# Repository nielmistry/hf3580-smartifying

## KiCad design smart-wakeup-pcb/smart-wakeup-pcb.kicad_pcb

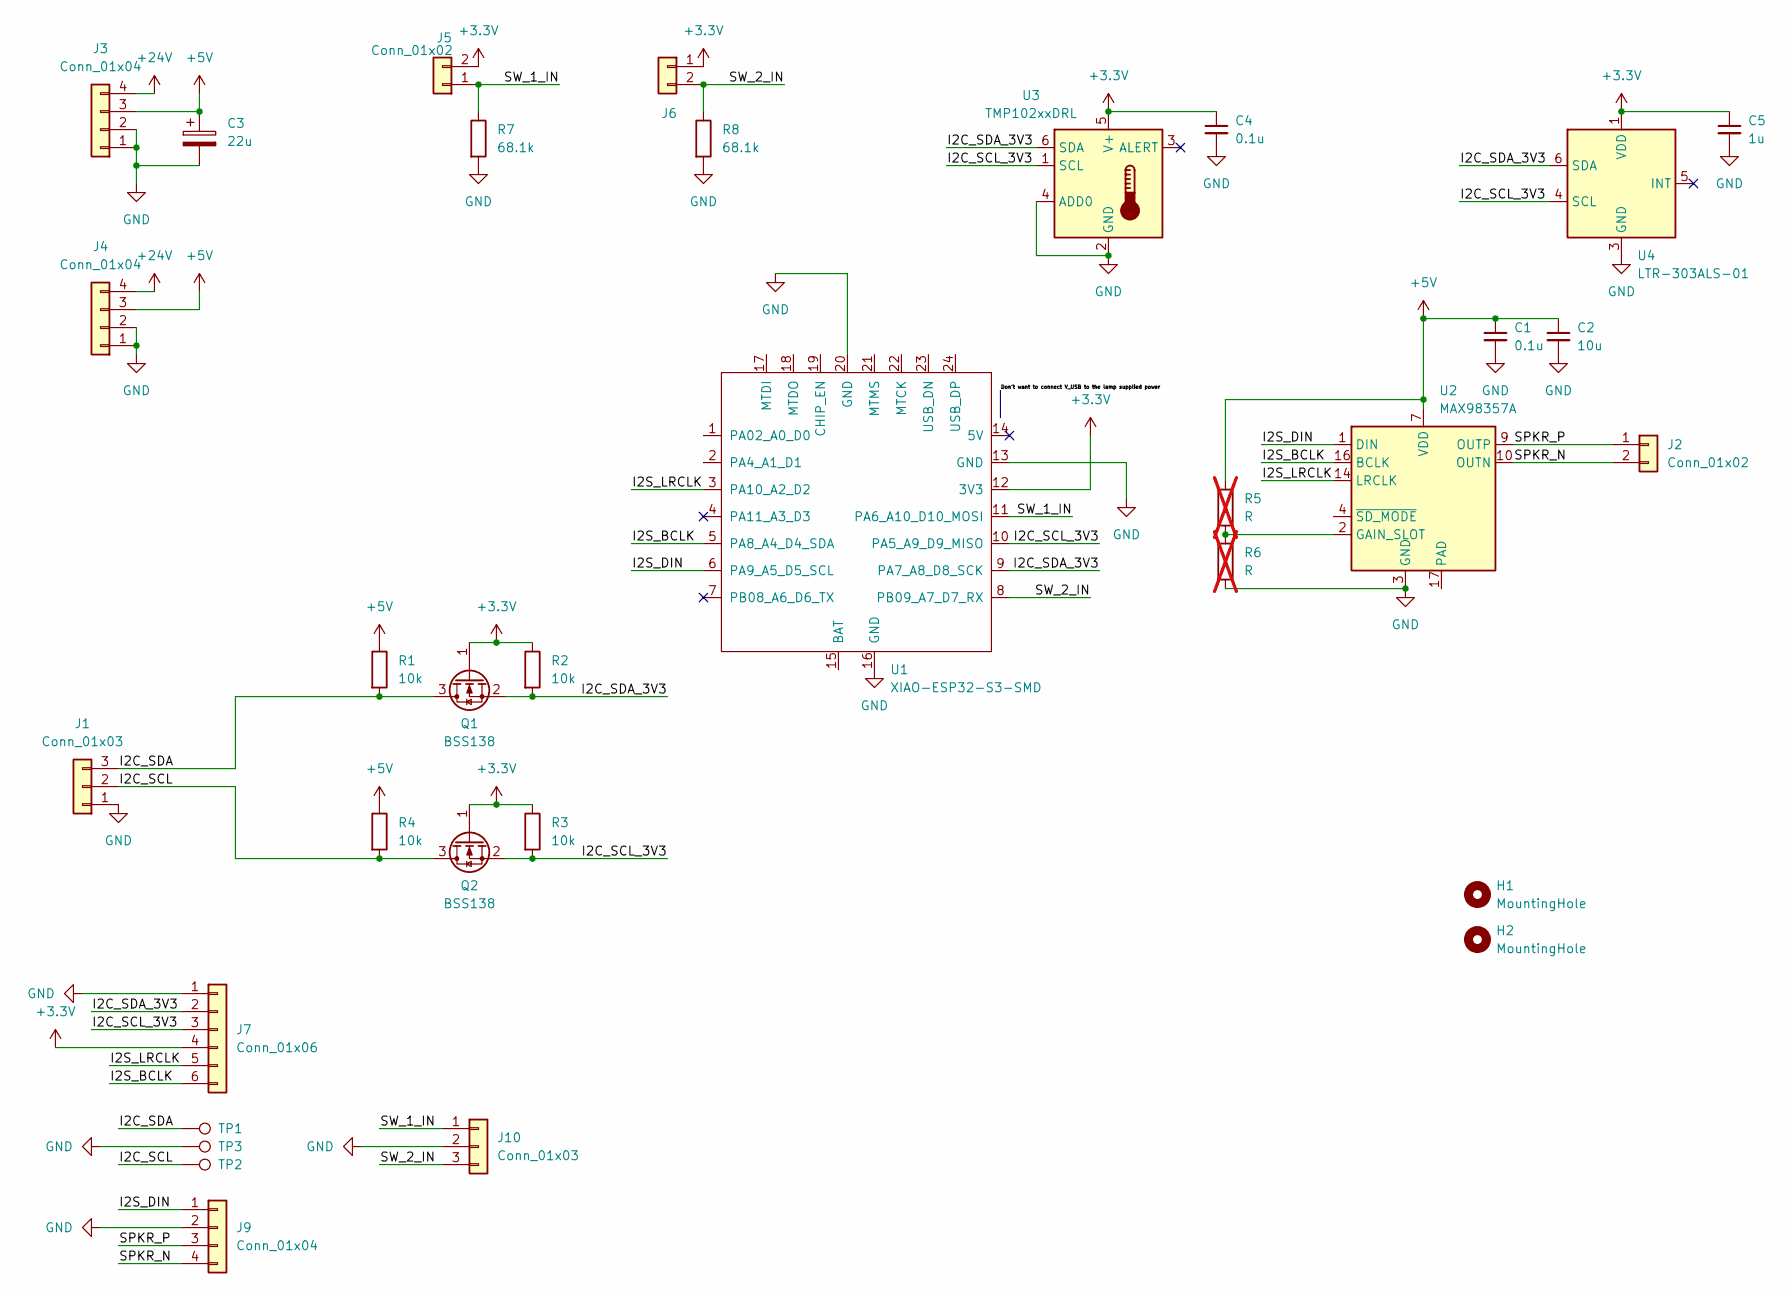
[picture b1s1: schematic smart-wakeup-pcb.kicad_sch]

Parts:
C1, C4: 0.1u; C_0603_1608Metric
C2: 10u; C_0603_1608Metric
C3: 22u; CP_Radial_D5.0mm_P2.00mm
C5: 1u; C_0603_1608Metric
H1, H2: MountingHole; MountingHole_2.2mm_M2
J1: Conn_01x03; JST_PH_S3B-PH-K_1x03_P2.00mm_Horizontal
J2: Conn_01x02; JST_PH_S2B-PH-K_1x02_P2.00mm_Horizontal
J3, J4: Conn_01x04; JST_PH_S4B-PH-K_1x04_P2.00mm_Horizontal
J5, J6: Conn_01x02; JST_PH_B2B-PH-K_1x02_P2.00mm_Vertical
J7: Conn_01x06; PinHeader_1x06_P1.00mm_Vertical
J9: Conn_01x04; PinHeader_1x04_P1.00mm_Vertical
J10: Conn_01x03; PinHeader_1x03_P1.00mm_Vertical
Q1, Q2: BSS138; SOT-23
R1, R2, R3, R4: 10k; R_0603_1608Metric
R5, R6: R; R_0603_1608Metric; not fitted
R7, R8: 68.1k; R_0603_1608Metric
TP1, TP2, TP3: TestPoint; TestPoint_Pad_D1.5mm
U1: XIAO-ESP32-S3-SMD
U2: MAX98357A; TQFN-16-1EP_3x3mm_P0.5mm_EP1.23x1.23mm
U3: TMP102xxDRL; SOT-563
U4: LTR-303ALS-01; Lite-On_LTR-303ALS-01

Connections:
+3.3V: C4.1, C5.1, J5.2, J6.1, J7.4, Q1.1 (G), Q2.1 (G), R2.1, R3.1, U1.12 (3V3), U3.5 (V+), U4.1 (VDD)
+5V: C1.1, C2.1, C3.1, J3.3, J4.3, R1.1, R4.1, R5.1, U2.7 (VDD), U2.8 (VDD)
+24V: J3.4, J4.4
/I2C_SCL: J1.2, Q2.3 (D), R4.2, TP2.1
/I2C_SCL_3V3: J7.3, Q2.2 (S), R3.2, U1.10 (PA5_A9_D9_MISO), U3.1 (SCL), U4.4 (SCL)
/I2C_SDA: J1.3, Q1.3 (D), R1.2, TP1.1
/I2C_SDA_3V3: J7.2, Q1.2 (S), R2.2, U1.9 (PA7_A8_D8_SCK), U3.6 (SDA), U4.6 (SDA)
/I2S_BCLK: J7.6, U1.5 (PA8_A4_D4_SDA), U2.16 (BCLK)
/I2S_DIN: J9.1, U1.6 (PA9_A5_D5_SCL), U2.1 (DIN)
/I2S_LRCLK: J7.5, U1.3 (PA10_A2_D2), U2.14 (LRCLK)
/SPKR_N: J2.2, J9.4, U2.10 (OUTN)
/SPKR_P: J2.1, J9.3, U2.9 (OUTP)
/SW_1_IN: J5.1, J10.1, R7.1, U1.11 (PA6_A10_D10_MOSI)
/SW_2_IN: J6.2, J10.3, R8.1, U1.8 (PB09_A7_D7_RX)
GND: C1.2, C2.2, C3.2, C4.2, C5.2, J1.1, J3.1, J3.2, J4.1, J4.2, J7.1, J9.2, J10.2, R6.2, R7.2, R8.2, TP3.1, U1.13 (GND), U1.16 (GND), U1.20 (GND), U2.3 (GND), U2.11 (GND), U2.15 (GND), U3.2 (GND), U3.4 (ADD0), U4.3 (GND)
unnamed: R5.2, R6.1, U2.2 (GAIN_SLOT)

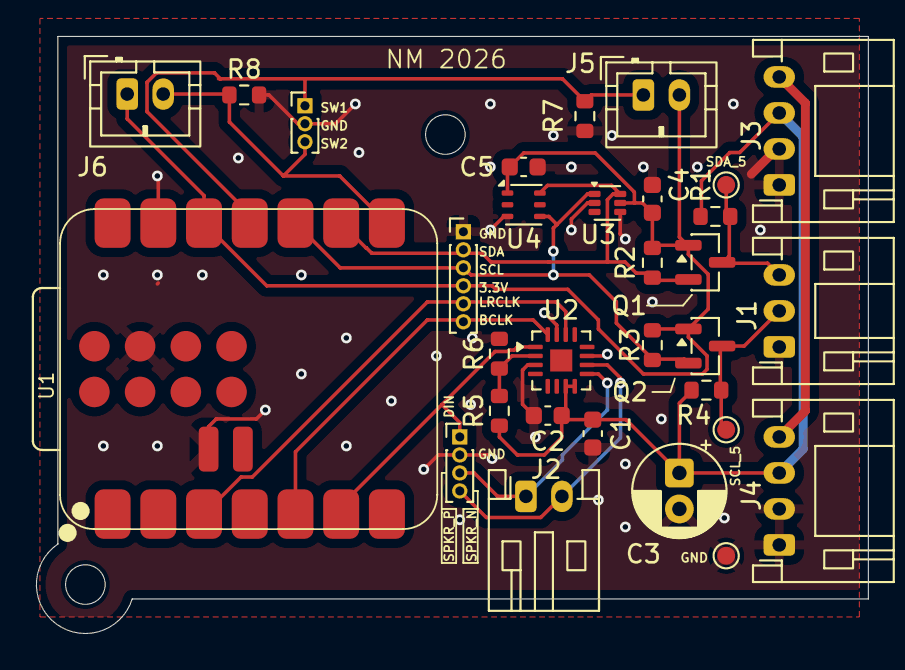
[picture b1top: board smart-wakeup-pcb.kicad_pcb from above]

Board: 2 copper layers, 46.2 x 33.2 mm, 33 parts (0 on the bottom side), 16 nets.

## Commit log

2026-01-05 add captures
2026-01-05 add esp, and pcb
2026-01-06 reroute
2026-01-18 drc, holes, lux sensor
2026-01-18 labeling and test points
